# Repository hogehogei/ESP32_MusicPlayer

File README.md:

# ESP32 MusicPlayer sample

## 概要
- Bluetooth Classic 接続 / SDカードから　音声再生可能なミュージックプレーヤ
- 音声再生機能は VS1053b に丸投げ

## ビルド方法
ESP-IDF v4.4 にてビルド確認。 esp32 wroom 32 (無印esp32) での設定。<br>
以下menuconfig設定要
- Compiler options -> Optimization Level (-O2)
- Component config -> Bluetooth ->
    - Bluetooth controller -> Bluetooth controller mode (BR/EDR Only)
    - Bluetooth Host -> (Bluedroid - Dual-mode)
    - Bluedroid Options ->
        - [*] Classic Bluetooth
        - [*] A2DP
        - [*] SPP
- Component config -> ESP System Settings ->  Panic handler behaviour (Print registers and halt)
- Serial flasher config -> Flash size (4MB)
- Partition Table -> PartitionTable (custom partition table CSV)

最適化有効にしないとBluetoothパケットドロップするので最適化必須、CPUクロックは160MHzで動作。<br>
パーティションは partition.csv を参照する。

ビルドコマンド<br>
```
$ cd main
$ idf.py build
```

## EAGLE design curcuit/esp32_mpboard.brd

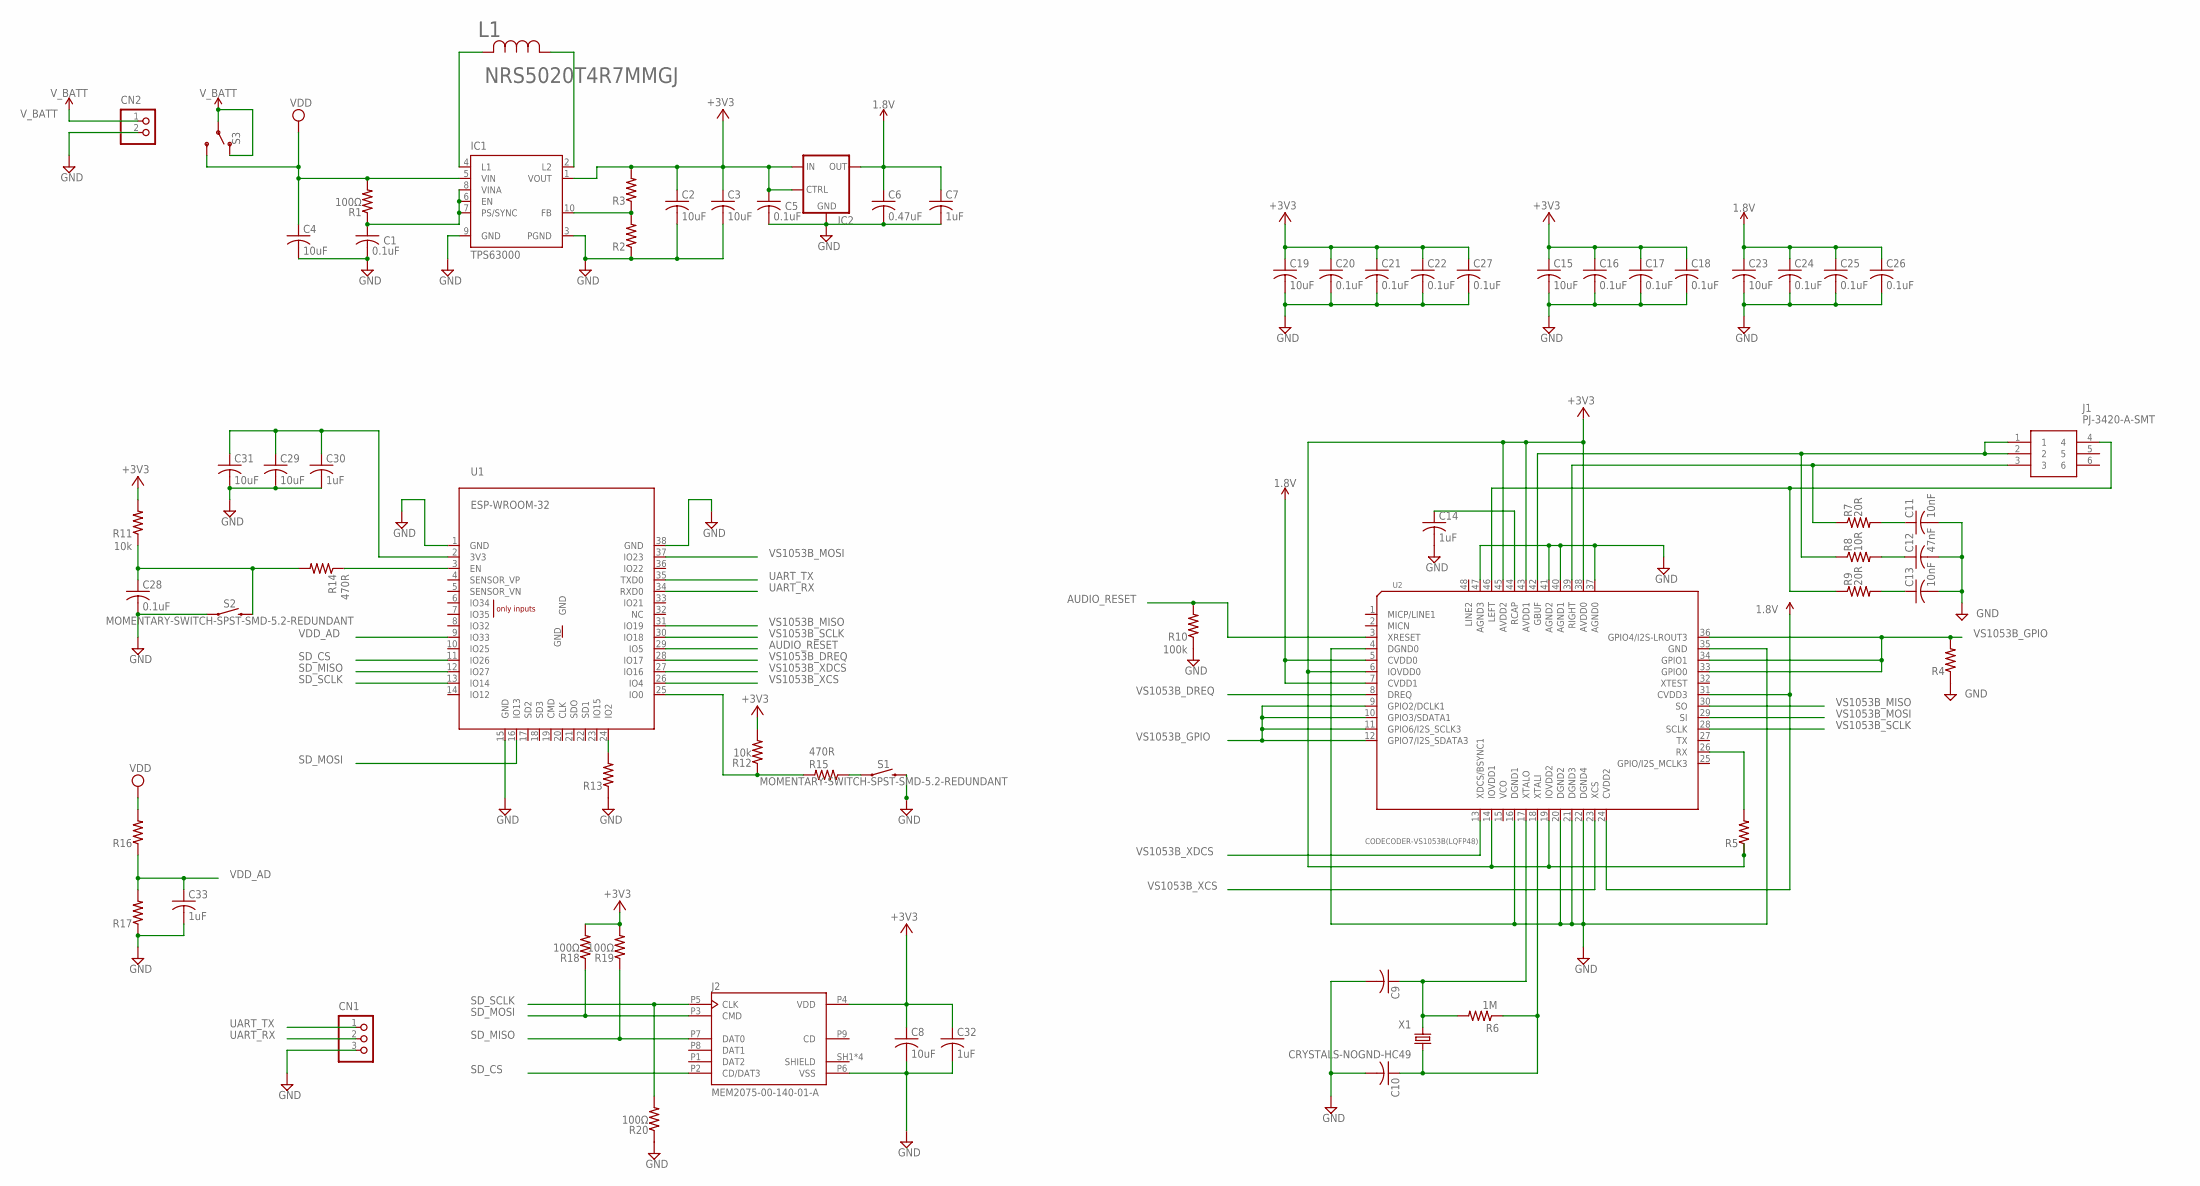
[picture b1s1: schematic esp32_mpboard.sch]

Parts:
C1, C5, C16, C17, C18, C20, C21, C22, C24, C25, C26, C27, C28: 0.1uF; C0603
C2, C3, C4, C8, C15, C19, C23, C29, C31: 10uF; C0805
C6: 0.47uF; C0603
C7, C14, C30, C32, C33: 1uF; C0603
C9, C10: C-USC0603; C0603
C11, C13: 10nF; C0603
C12: 47nF; C0603
CN1: B3B-XH-A
CN2: B2B-XH-A
IC1: TPS63000; DRC-S-PVSON-N10_MANUALSOLDER
IC2: NJM12888F1812DBV; SOT23-5
J1: PJ-3420-A-SMT; PJ3420ASMT
J2: MEM2075-00-140-01-A; GCT_MEM2075-00-140-01-A
L1: NRS5020T4R7MMGJ; IND_TAIYO_NRS5020
R1, R18, R19, R20: 100Ω; R0603
R2, R3, R4, R5, R13, R16, R17: R-US_R0603; R0603
R6: 1M; R0603
R7, R9: 20R; R0603
R8: 10R; R0603
R10: 100k; R0603
R11, R12: 10k; R0603
R14, R15: 470R; R0603
S1, S2: MOMENTARY-SWITCH-SPST-SMD-5.2-REDUNDANT; TACTILE_SWITCH_SMD_5.2MM
S3: SWITCH-SPDT-PTH-11.6X4.0MM; SWITCH_SPDT_PTH_11.6X4.0MM
U1: ESP-WROOM-32
U2: CODECODER-VS1053B(LQFP48); LQFP48-0.5-7X7MM
X1: CRYSTALS-NOGND-HC49; HC49

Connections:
1.8V: C6.1, C7.1, C23.1, C24.1, C25.1, C26.1, IC2.5 (OUT), U2.5 (CVDD0), U2.7 (CVDD1), U2.24 (CVDD2), U2.31 (CVDD3)
1.8V1: C9.1, R6.2, U2.17 (XTALO), X1.2
3V3: C2.1, C3.1, C5.1, C8.1, C15.1, C16.1, C17.1, C18.1, C19.1, C20.1, C21.1, C22.1, C27.1, C29.1, C30.1, C31.1, C32.1, IC1.1 (VOUT), IC2.1 (IN), IC2.3 (CONTROL), J2.P4 (VDD), R3.2, R5.1, R5.2, R12.2, R18.2, R19.2, U1.2 (3V3), U2.6 (IOVDD0), U2.14 (IOVDD1), U2.19 (IOVDD2), U2.26 (RX), U2.38 (AVDD0), U2.43 (AVDD1), U2.45 (AVDD2)
+3V3: R11.2
AUDIO_RESET: R10.2, U1.29 (IO5), U2.3 (XRESET)
GND: C1.2, C2.2, C3.2, C4.2, C5.2, C6.2, C7.2, C8.2, C9.2, C10.2, C11.2, C12.2, C13.2, C14.2, C15.2, C16.2, C17.2, C18.2, C19.2, C20.2, C21.2, C22.2, C23.2, C24.2, C25.2, C26.2, C27.2, C28.2, C29.2, C30.2, C31.2, C32.2, C33.2, CN1.3, CN2.2, IC1.3 (PGND), IC1.9 (GND), IC2.2 (GND), J2.P6 (VSS), R2.1, R4.1, R10.1, R13.1, R17.1, R20.1, S1.3 (2), S1.4 (2), S2.1, S2.2 (1), U1.1 (GND), U1.15 (GND), U1.38 (GND), U2.4 (DGND0), U2.16 (DGND1), U2.20 (DGND2), U2.21 (DGND3), U2.22 (DGND4), U2.35 (GND), U2.37 (AGND0), U2.40 (AGND1), U2.41 (AGND2), U2.47 (AGND3)
GND1: C10.1, R6.1, U2.18 (XTALI), X1.1
unnamed: IC1.4 (L1), L1.2
unnamed: IC1.2 (L2), L1.1
unnamed: C1.1, IC1.6 (EN), IC1.7 (PS/SYNC), IC1.8 (VINA), R1.1
unnamed: IC1.10 (FB), R2.2, R3.1
unnamed: J1.4, R9.1, U2.46 (LEFT)
unnamed: J1.1, J1.2, R8.1, U2.42 (GBUF)
unnamed: J1.3, R7.1, U2.39 (RIGHT)
unnamed: C12.1, R8.2
unnamed: C13.1, R9.2
unnamed: C11.1, R7.2
unnamed: R12.1, R15.2, U1.25 (IO0)
unnamed: C14.1, U2.44 (RCAP)
unnamed: C28.1, R11.1, R14.2, S2.3 (2), S2.4 (2)
unnamed: R13.2, U1.24 (IO2)
unnamed: R14.1, U1.3 (EN)
unnamed: R15.1, S1.1, S1.2 (1)
SD_CS: J2.P2 (CD/DAT3), U1.11 (IO26)
SD_MISO: J2.P7 (DAT0), R19.1, U1.12 (IO27)
SD_MOSI: J2.P3 (CMD), R18.1, U1.16 (IO13)
SD_SCLK: J2.P5 (CLK), R20.2, U1.13 (IO14)
SHIELD: J2.SH1 (SHIELD), J2.SH2 (SHIELD), J2.SH3 (SHIELD), J2.SH4 (SHIELD)
UART_RX: CN1.2, U1.34 (RXD0)
UART_TX: CN1.1, U1.35 (TXD0)
VCO: U2.15 (VCO)
VDD: C4.1, IC1.5 (VIN), R1.2, R16.2, S3.3 (S)
VDD_AD: C33.1, R16.1, R17.2, U1.9 (IO33)
VS1053B_DREQ: U1.28 (IO17), U2.8 (DREQ)
VS1053B_GPIO: R4.2, U2.9 (GPIO2/DCLK1), U2.10 (GPIO3/SDATA1), U2.11 (GPIO6/I2S_SCLK3), U2.12 (GPIO7/I2S_SDATA3), U2.33 (GPIO0), U2.34 (GPIO1), U2.36 (GPIO4/I2S-LROUT3)
VS1053B_MISO: U1.31 (IO19), U2.30 (SO)
VS1053B_MOSI: U1.37 (IO23), U2.29 (SI)
VS1053B_SCLK: U1.30 (IO18), U2.28 (SCLK)
VS1053B_XCS: U1.26 (IO4), U2.23 (XCS)
VS1053B_XDCS: U1.27 (IO16), U2.13 (XDCS/BSYNC1)
V_BATT: CN2.1, S3.1 (O), S3.2

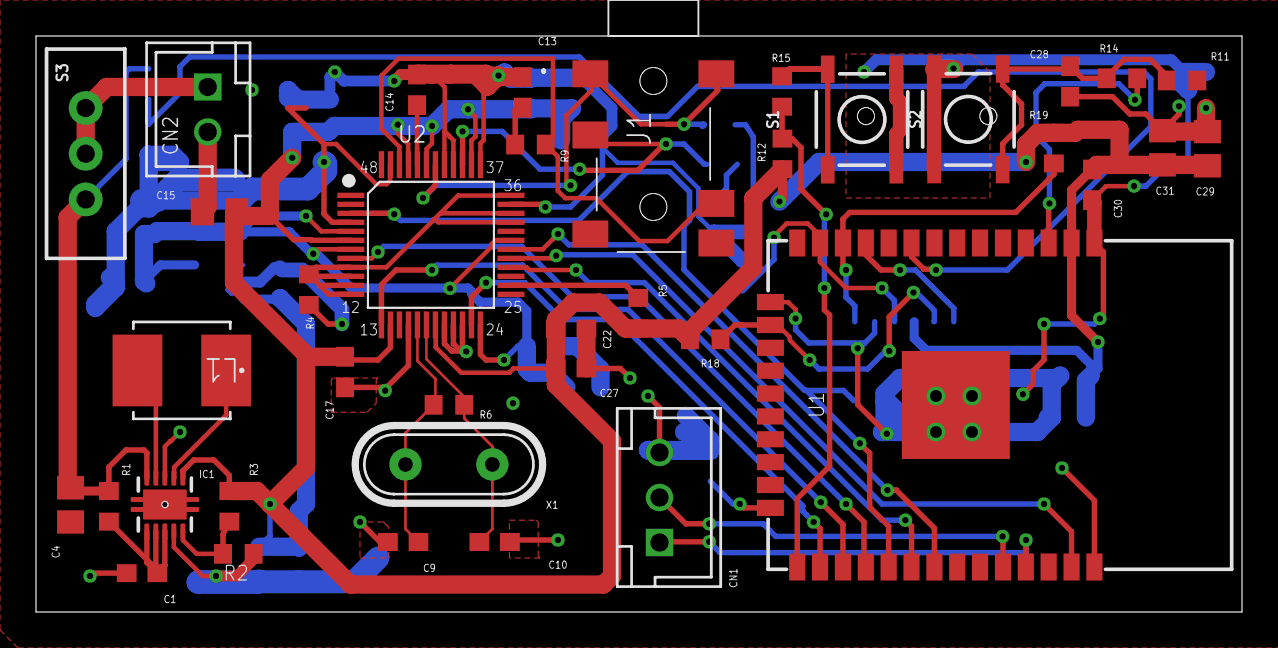
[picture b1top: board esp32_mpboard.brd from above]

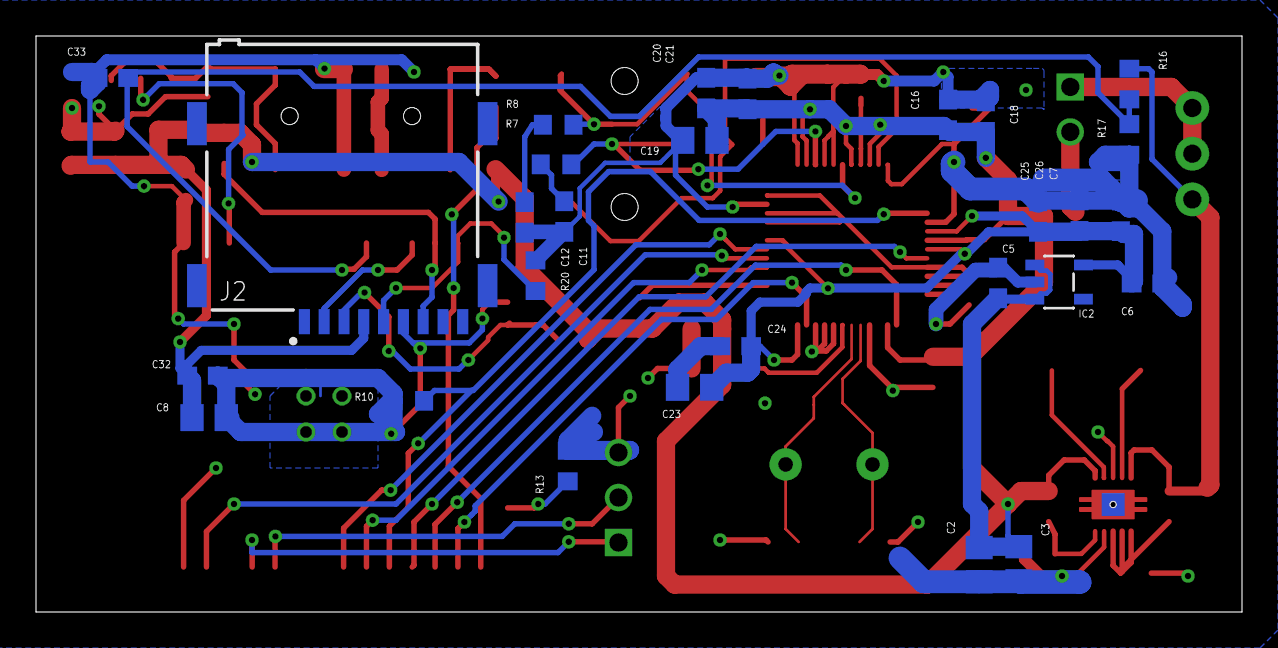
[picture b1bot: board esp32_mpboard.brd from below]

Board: 2 copper layers, 67.0 x 32.0 mm, 66 parts (28 on the bottom side), 39 nets.

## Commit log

2020-01-12 ・Initial Commit
2020-01-26 Initial Commit.
2020-02-03 ・bluetooth audio 受信部など実装 まだ動かない
2020-02-04 ・Bluetooth 初期化コードを修正。 ・menuconfig で Bluetooth のコンポーネント設定を変更。 ・タスクループにDelayを追加。
2020-02-24 ・ Bluetooth で音楽再生できるようになった
2020-02-27 ・回路図作成中
2020-06-20 ・SDカード読み込み処理を追加 ・ガーバーファイルを更新
2020-07-12 ・ひとまず完成 SDカードとBluetoothから音楽再生可能になる
2021-08-13 ・BLE起動時のbrownout対策に PHY の出力低減設定追加 ・パーティション設定をカスタム仕様にした
2021-08-13 ・README変更
2021-08-13 ・README修正
2023-12-26 ESP-IDF v4.4 対応
2023-12-26 SDカード/BT初期化失敗時に音楽再生タスクを停止する処理を追加
2023-12-26 プレーや種別切り替え時に、VS1053bもハードウェアリセットする
2023-12-26 ドライバ初期化順修正
2023-12-27 abort()時に自動再起動しないようにする
2023-12-28 入力電圧検出抵抗を修正し5V入力まで対応

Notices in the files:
parts and their libraries:
SparkFun-Switches: Licensing: Creative Commons ShareAlike 4.0 International - https://creativecommons.org/licenses/by-sa/4.0
